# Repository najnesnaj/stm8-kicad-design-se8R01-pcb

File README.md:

# stm8-kicad-design-se8R01-pcb
PCB kicad stm8 se8r01

this is my design in kicad of a pcb which contains a stm8 microcontroller smd component and a SE8R01 wireless device

I send the design of to oshpark and it works! 

The design uses as little components as possible. The led had no resistor, but I use pwm to control it.
I bought everything from a well known chinese website.

The most expensive part was the PCB board -- 7 dollar for 3 boards.

The file stm8.pdf describes the connections, which I use in the programming.

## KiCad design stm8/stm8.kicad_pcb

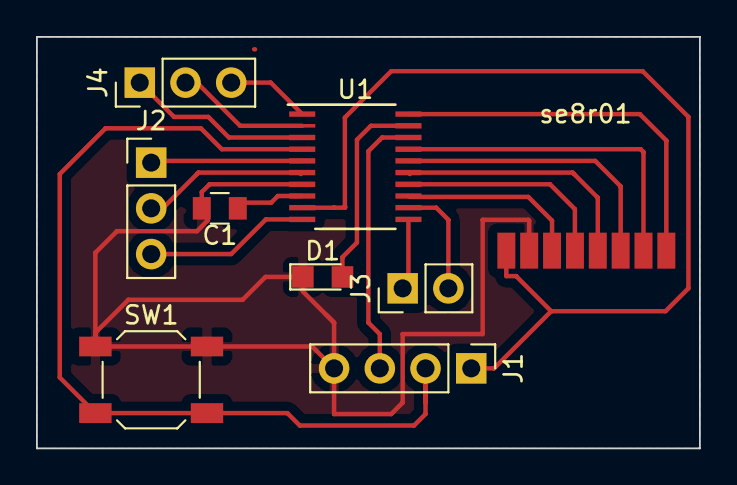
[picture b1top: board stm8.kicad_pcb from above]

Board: 2 copper layers, 36.8 x 22.9 mm, 9 parts (0 on the bottom side), 20 nets.

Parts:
C1: 1uF; C_0805
D1: LED_Small; LED_0805
J1: CONN_01X04_MALE; Pin_Header_Straight_1x04_Pitch2.54mm
J2, J4: CONN_01X03; Pin_Header_Straight_1x03_Pitch2.54mm
J3: CONN_01X02_MALE; Pin_Header_Straight_1x02_Pitch2.54mm
SW1: SW_DPST; SW_SPST_SKQG
U1: STM8S003F3P; TSSOP-20_4.4x6.5mm_Pitch0.65mm
se8r01: SE8R01; SE08R01

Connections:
+3V3: J1.1, U1.9, se8r01.1
GND: C1.2, D1.1, J1.4, SW1.1, U1.7, se8r01.2
unnamed: C1.1, U1.8
unnamed: D1.2, U1.19
unnamed: J1.2, SW1.2, U1.4
unnamed: J1.3, U1.18
unnamed: J2.1, U1.5
unnamed: J2.2, U1.6
unnamed: J2.3, U1.10
unnamed: J3.1, U1.11
unnamed: J3.2, U1.12
unnamed: J4.1, U1.3
unnamed: J4.2, U1.2
unnamed: J4.3, U1.1
unnamed: U1.13, se8r01.3
unnamed: U1.14, se8r01.4
unnamed: U1.15, se8r01.5
unnamed: U1.16, se8r01.6
unnamed: U1.17, se8r01.7
unnamed: U1.20, se8r01.8

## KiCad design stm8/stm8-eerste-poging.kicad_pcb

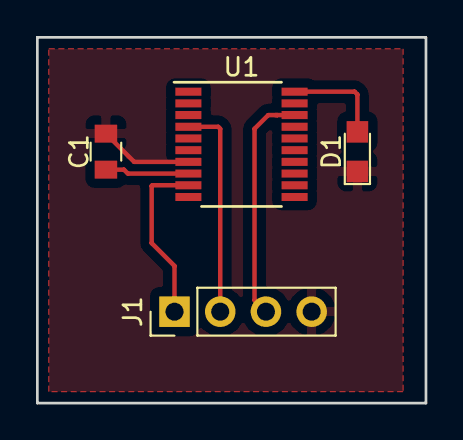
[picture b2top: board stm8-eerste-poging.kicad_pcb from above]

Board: 2 copper layers, 21.6 x 20.3 mm, 4 parts (0 on the bottom side), 6 nets.

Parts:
C1: 1uF; C_0805
D1: LED_Small; LED_0805
J1: CONN_01X04_MALE; Pin_Header_Straight_1x04_Pitch2.54mm
U1: STM8S003F3P; TSSOP-20_4.4x6.5mm_Pitch0.65mm

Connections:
+3V3: J1.1, U1.9
GND: C1.2, D1.1, J1.4, U1.7
unnamed: C1.1, U1.8
unnamed: D1.2, U1.20
unnamed: J1.2, U1.4
unnamed: J1.3, U1.18
